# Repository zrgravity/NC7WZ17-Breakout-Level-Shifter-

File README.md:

# NC7WZ17 Breakout (Level Shifter)

This uses an On Semiconductor NC7WZ17 Schmitt Trigger Non-inverting Dual Buffer. It can be used for 3.3V to 5V level conversion, or 5V to 3.3V level conversion.

Output voltage is at VCC (apply the desired output high voltage to VCC).

Board size is 0.4" x 0.45"

# Electrical Characteristics of NC7WZ17 (25C)
Supply voltage: 1.65V to 5.5V typical (7V max)
Propagation delay: 3.6ns typical into 50pf at 5V (5.6us max)
24mA output current at 3V
Over-voltage tolerant inputs (up to 7V, 5.5V max recommended)
Quiescient Current: 1uA typ, 10uA max

***Schmitt Trigger***
Positive threshold voltage (3V): 1.74V typ, 2.2V max
Negative threshold voltage (3V): 0.60V min, 0.98V typ

Positive threshold voltage (5.5V): 2.88V typ, 3.6V max
Negative threshold voltage (5.5V): 1.20V min, 1.68V typ

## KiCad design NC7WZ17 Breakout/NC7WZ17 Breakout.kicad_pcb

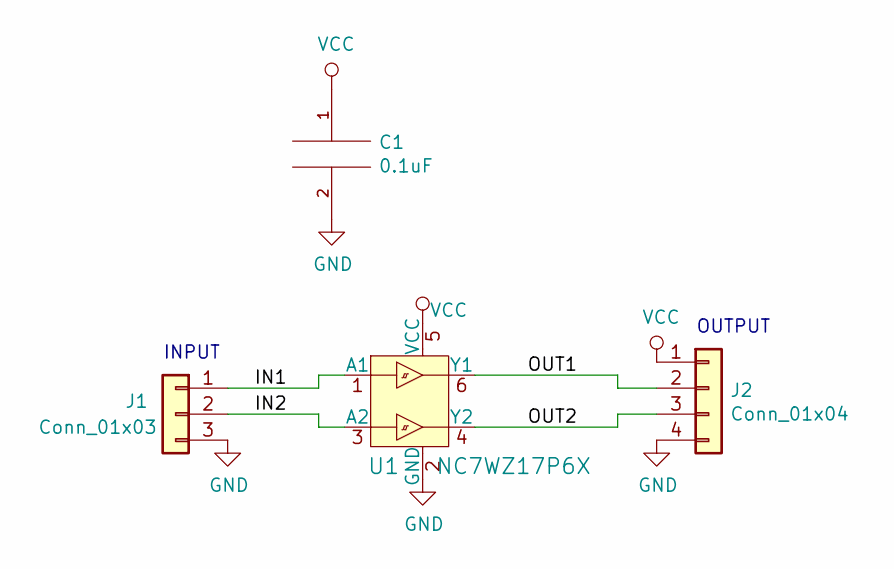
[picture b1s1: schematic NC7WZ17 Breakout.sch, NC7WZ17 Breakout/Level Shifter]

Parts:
C1: 0.1uF; C_0603_1608Metric
J1: Conn_01x03; PinHeader_1x03_P2.54mm_Vertical
J2: Conn_01x04; PinHeader_1x04_P2.54mm_Vertical
U1: NC7WZ17P6X; SOT-363; MPN NC7WZ17P6X; Digi-Key_PN NC7WZ17P6XCT-ND

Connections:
/IN1: J1.1, U1.1 (A1)
/IN2: J1.2, U1.3 (A2)
/OUT1: J2.2, U1.6 (Y1)
/OUT2: J2.3, U1.4 (Y2)
GND: C1.2, J1.3, J2.4, U1.2 (GND)
VCC: C1.1, J2.1, U1.5 (VCC)

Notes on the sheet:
OUTPUT
INPUT

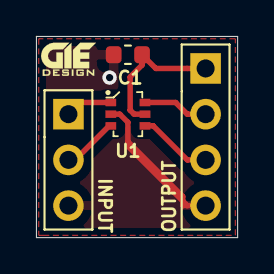
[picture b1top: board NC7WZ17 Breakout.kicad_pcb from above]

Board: 2 copper layers, 11.2 x 11.2 mm, 4 parts (0 on the bottom side), 6 nets.

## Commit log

2019-10-10 Create PCB folder
2019-10-10 Add datasheet
2019-10-10 Schematic done
2019-10-10 0.1uF capacitor value
2019-10-10 Create PCB
2019-10-10 Add layout PDFs and Dimensions
2019-10-10 Add gerber files (1A)
2019-10-10 Add BOM
2019-10-29 Change header to header spacing to 0.3", Update header and IC silkscreen
2019-10-29 Move silkscreen
